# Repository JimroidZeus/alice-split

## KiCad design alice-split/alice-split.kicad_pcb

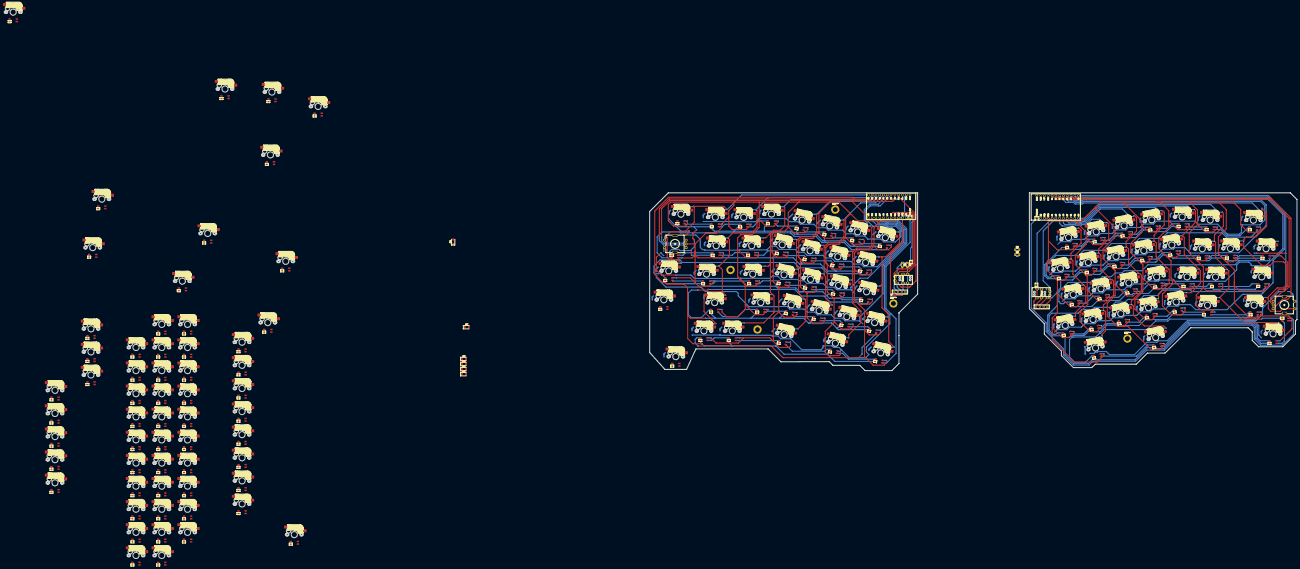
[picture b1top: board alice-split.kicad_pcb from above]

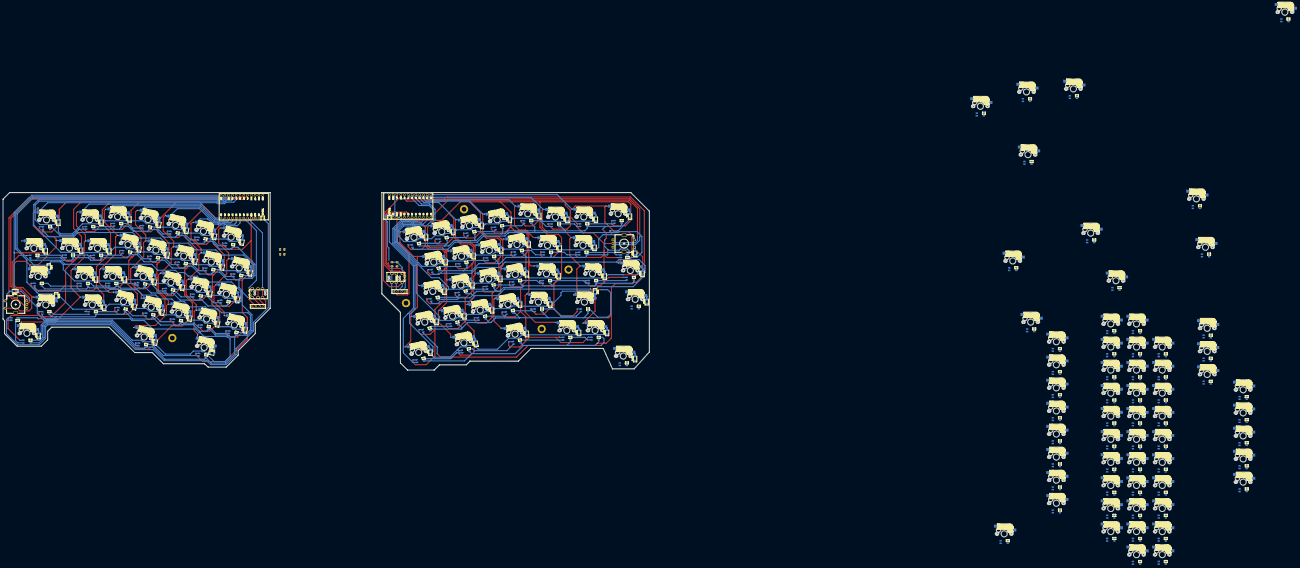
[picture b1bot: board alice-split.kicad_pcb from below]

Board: 2 copper layers, 434.2 x 119.2 mm, 215 parts (69 on the bottom side), 182 nets.

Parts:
D1, D2, D3, D4, D5, D6, D7, D8, D9, D10, D11, D12, D13, D14, D15, D16, D17, D18, D19, D20, D21, D22, D23, D24, D25, D26, D27, D28, D29, D30, D31, D32, D33, D34, D35, D36, D37, D38, D39, D40, D41, D42, D43, D44, D45, D46, D47, D48, D49, D50, D51, D52, D53, D54, D55, D56, D57, D58, D59, D60, D61, D62, D63, D64, D65, D66, D67, D68, D69, D70, D71, D72, D73, D74: D_Small; D_1206_3216Metric
D_ENC_L1: LED_sk2812_SM; SK6812MINI_underglow_dev
D_ENC_R1: LED_sk2812_SM; SK6812MINI_underglow_dev
J1, J4: MJ-4PP-9-Lily58-cache-Lily58_Pro-rescue; MJ-4PP-9
J2, J3: OLED-Lily58-cache; OLED_4Pin
JP1, JP2: Jumper-Device; Jumper
R1, R2, R3, R4: R_Small; R_1206_DoubleSided
SW38, SW39, SW40, SW41, SW42, SW43, SW44, SW45, SW46, SW47, SW48, SW49, SW50, SW51, SW52, SW53, SW54, SW55, SW56, SW57, SW58, SW59, SW60, SW61, SW62, SW63, SW64, SW65, SW66, SW67, SW68, SW69, SW70, SW71, SW72, SW73, SW74, SW75, SW76, SW77, SW78, SW79, SW80, SW81, SW82, SW83, SW84, SW85, SW86, SW87, SW88, SW89: SW_PUSH-MX_W_LED; SK6812MINI_and_cherry
SW_0, SW_1, SW_2, SW_3, SW_4, SW_5, SW_6, SW_7, SW_8, SW_9: SW_PUSH-MX_W_LED; SK6812MINI_and_cherry
SW_A1: SW_PUSH-MX_W_LED; SK6812MINI_and_cherry
SW_BCKSLSH1: SW_PUSH-MX_W_LED; SK6812MINI_and_cherry
SW_BCKSPC1: SW_PUSH-MX_W_LED; SK6812MINI_and_cherry
SW_B_L1: SW_PUSH-MX_W_LED; SK6812MINI_and_cherry
SW_B_R1: SW_PUSH-MX_W_LED; SK6812MINI_and_cherry
SW_C1: SW_PUSH-MX_W_LED; SK6812MINI_and_cherry
SW_CAPS1: SW_PUSH-MX_W_LED; SK6812MINI_and_cherry
SW_COLON1: SW_PUSH-MX_W_LED; SK6812MINI_and_cherry
SW_COMMA1: SW_PUSH-MX_W_LED; SK6812MINI_and_cherry
SW_CTRL_L1: SW_PUSH-MX_W_LED; SK6812MINI_and_cherry
SW_C_BRACE1: SW_PUSH-MX_W_LED; SK6812MINI_and_cherry
SW_D1: SW_PUSH-MX_W_LED; SK6812MINI_and_cherry
SW_E1: SW_PUSH-MX_W_LED; SK6812MINI_and_cherry
SW_ENC_L1: RotaryEncoder_Switch; RotaryEncoder_Alps_EC11E-Switch_Vertical_H20mm-keebio_modif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
SW_ENC_R1: RotaryEncoder_Switch; RotaryEncoder_Alps_EC11E-Switch_Vertical_H20mm-keebio_modif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
SW_ENTER1: SW_PUSH-MX_W_LED; SK6812MINI_and_cherry
SW_EQUALS1: SW_PUSH-MX_W_LED; SK6812MINI_and_cherry
SW_ESC1: SW_PUSH-MX_W_LED; SK6812MINI_and_cherry
SW_F1, SW_F2, SW_F3, SW_F4, SW_F5, SW_F6, SW_F7, SW_F8: SW_PUSH-MX_W_LED; SK6812MINI_and_cherry
SW_FN1: SW_PUSH-MX_W_LED; SK6812MINI_and_cherry
SW_G1: SW_PUSH-MX_W_LED; SK6812MINI_and_cherry
SW_H1: SW_PUSH-MX_W_LED; SK6812MINI_and_cherry
SW_I1: SW_PUSH-MX_W_LED; SK6812MINI_and_cherry
SW_J1: SW_PUSH-MX_W_LED; SK6812MINI_and_cherry
SW_K1: SW_PUSH-MX_W_LED; SK6812MINI_and_cherry
SW_L1: SW_PUSH-MX_W_LED; SK6812MINI_and_cherry
SW_M1: SW_PUSH-MX_W_LED; SK6812MINI_and_cherry
SW_MACRO1, SW_MACRO2, SW_MACRO3, SW_MACRO4: SW_PUSH-MX_W_LED; SK6812MINI_and_cherry
SW_MINUS1: SW_PUSH-MX_W_LED; SK6812MINI_and_cherry
SW_MOD_L1: SW_PUSH-MX_W_LED; SK6812MINI_and_cherry
SW_MOD_R1: SW_PUSH-MX_W_LED; SK6812MINI_and_cherry
SW_N1: SW_PUSH-MX_W_LED; SK6812MINI_and_cherry
SW_O1: SW_PUSH-MX_W_LED; SK6812MINI_and_cherry
SW_OPT1: SW_PUSH-MX_W_LED; SK6812MINI_and_cherry
SW_O_BRACE1: SW_PUSH-MX_W_LED; SK6812MINI_and_cherry
SW_P1: SW_PUSH-MX_W_LED; SK6812MINI_and_cherry
SW_PERIOD1: SW_PUSH-MX_W_LED; SK6812MINI_and_cherry
SW_Q1: SW_PUSH-MX_W_LED; SK6812MINI_and_cherry
SW_QUOTE1: SW_PUSH-MX_W_LED; SK6812MINI_and_cherry
SW_R1: SW_PUSH-MX_W_LED; SK6812MINI_and_cherry
SW_S1: SW_PUSH-MX_W_LED; SK6812MINI_and_cherry
SW_SHIFT_L1: SW_PUSH-MX_W_LED; SK6812MINI_and_cherry
SW_SHIFT_R1: SW_PUSH-MX_W_LED; SK6812MINI_and_cherry
SW_SLASH1: SW_PUSH-MX_W_LED; SK6812MINI_and_cherry
SW_SPC_L1: SW_PUSH-MX_W_LED; SK6812MINI_and_cherry
SW_SPC_R1: SW_PUSH-MX_W_LED; SK6812MINI_and_cherry
SW_T1: SW_PUSH-MX_W_LED; SK6812MINI_and_cherry
SW_TAB1: SW_PUSH-MX_W_LED; SK6812MINI_and_cherry
SW_TILDE1: SW_PUSH-MX_W_LED; SK6812MINI_and_cherry
SW_U1: SW_PUSH-MX_W_LED; SK6812MINI_and_cherry
SW_V1: SW_PUSH-MX_W_LED; SK6812MINI_and_cherry
SW_W1: SW_PUSH-MX_W_LED; SK6812MINI_and_cherry
SW_X1: SW_PUSH-MX_W_LED; SK6812MINI_and_cherry
SW_Y1: SW_PUSH-MX_W_LED; SK6812MINI_and_cherry
SW_Z1: SW_PUSH-MX_W_LED; SK6812MINI_and_cherry
U1: Sparkfun_Pro_Micro; ArduinoProMicro
U2: ProMicro_2-Lily58-cache-Lily58_Pro-rescue; ArduinoProMicro

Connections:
/COL0: SW_6.6, SW_B_L1.6, SW_FN1.6, SW_G1.6, SW_T1.6, U1.19 (A2(PF5))
/COL1: SW_5.6, SW_F8.6, SW_R1.6, SW_SPC_L1.6, SW_V1.6, U1.18 (A1(PF6))
/COL2: SW_4.6, SW_C1.6, SW_D1.6, SW_E1.6, SW_MOD_L1.6, U1.17 (A0(PF7))
/COL3: SW_3.6, SW_OPT1.6, SW_S1.6, SW_W1.6, SW_X1.6, U1.16 (D15(PB1))
/COL4: SW_2.6, SW_A1.6, SW_CTRL_L1.6, SW_Q1.6, SW_Z1.6, U1.15 (D14(PB3))
/COL5: SW_1.6, SW_CAPS1.6, SW_MACRO3.6, SW_SHIFT_L1.6, SW_TAB1.6, U1.14 (D16(PB2))
/COL6: SW_ENC_L1.S1, SW_ESC1.6, SW_MACRO1.6, SW_MACRO2.6, SW_TILDE1.6, U1.13 (D10(PB6))
/DATA: JP1.1, U1.2 (RX(PD2))
/ENCA: SW_ENC_L1.A, U1.20 (A3(PF4))
/ENCB: SW_ENC_L1.B, U1.12 (D9(PB5))
/ENC_S2: D38.2 (A), SW_ENC_L1.S2
/LEDs: SW_FN1.3 (DIN), U1.1 (TX(PD3))
/ROW0: D33.1 (K), D34.1 (K), D35.1 (K), D36.1 (K), D37.1 (K), D40.1 (K), D74.1 (K), U1.7 (D4(PD4))
/ROW1: D27.1 (K), D28.1 (K), D29.1 (K), D30.1 (K), D31.1 (K), D32.1 (K), D39.1 (K), U1.8 (D5(PC6))
/ROW2: D21.1 (K), D22.1 (K), D23.1 (K), D24.1 (K), D25.1 (K), D26.1 (K), D38.1 (K), U1.9 (D6(PD7))
/ROW3: D1.1 (K), D15.1 (K), D16.1 (K), D17.1 (K), D18.1 (K), D19.1 (K), D20.1 (K), U1.10 (D7(PE6))
/ROW4: D8.1 (K), D9.1 (K), D10.1 (K), D11.1 (K), D12.1 (K), D13.1 (K), D14.1 (K), U1.11 (D8(PB4))
/Right Hand Side/COL0: SW_BCKSPC1.6, SW_C_BRACE1.6, SW_ENC_R1.S1, SW_ENTER1.6, SW_SHIFT_R1.6, U2.18 (A1(PF6))
/Right Hand Side/COL1: SW_EQUALS1.6, SW_MACRO4.6, SW_O_BRACE1.6, SW_QUOTE1.6, SW_SLASH1.6, U2.12 (D9(PB5))
/Right Hand Side/COL2: SW_COLON1.6, SW_MINUS1.6, SW_P1.6, SW_PERIOD1.6, U2.11 (D8(PB4))
/Right Hand Side/COL3: SW_0.6, SW_COMMA1.6, SW_L1.6, SW_O1.6, U2.10 (D7(PE6))
/Right Hand Side/COL4: SW_9.6, SW_I1.6, SW_K1.6, SW_M1.6, SW_MOD_R1.6, U2.9 (D6(PD7))
/Right Hand Side/COL5: SW_8.6, SW_J1.6, SW_N1.6, SW_SPC_R1.6, SW_U1.6, U2.8 (D5(PC6))
/Right Hand Side/COL6: SW_7.6, SW_BCKSLSH1.6, SW_B_R1.6, SW_H1.6, SW_Y1.6, U2.7 (D4(PD4))
/Right Hand Side/DATA: JP2.2, U2.2 (RX(PD2))
/Right Hand Side/ENCA: SW_ENC_R1.A, U2.20 (A3(PF4))
/Right Hand Side/ENCB: SW_ENC_R1.B, U2.19 (A2(PF5))
/Right Hand Side/ENC_S2: D72.2 (A), SW_ENC_R1.S2
/Right Hand Side/LEDs: D_ENC_R1.3 (DIN), U2.1 (TX(PD3))
/Right Hand Side/ROW0: D55.1 (K), D70.1 (K), D71.1 (K), D72.1 (K), D73.1 (K), U2.13 (D10(PB6))
/Right Hand Side/ROW1: D63.1 (K), D64.1 (K), D65.1 (K), D66.1 (K), D67.1 (K), D68.1 (K), D69.1 (K), U2.14 (D16(PB2))
/Right Hand Side/ROW2: D56.1 (K), D57.1 (K), D58.1 (K), D59.1 (K), D60.1 (K), D61.1 (K), D62.1 (K), U2.15 (D14(PB3))
/Right Hand Side/ROW3: D48.1 (K), D49.1 (K), D50.1 (K), D51.1 (K), D52.1 (K), D53.1 (K), D54.1 (K), U2.16 (D15(PB1))
/Right Hand Side/ROW4: D41.1 (K), D42.1 (K), D43.1 (K), D44.1 (K), D45.1 (K), D46.1 (K), D47.1 (K), U2.17 (A0(PF7))
/Right Hand Side/SCL: J3.2, J4.4, R4.2, U2.6 (SCL(PD0))
/Right Hand Side/SDA: J3.1, J4.3, JP2.1, R3.2, U2.5 (SDA(PD1))
/Right Hand Side/VCC: D_ENC_R1.2 (VSS), J3.3, J4.1, R3.1, R4.1, SW_0.2 (VSS), SW_7.2 (VSS), SW_8.2 (VSS), SW_9.2 (VSS), SW_BCKSLSH1.2 (VSS), SW_BCKSPC1.2 (VSS), SW_B_R1.2 (VSS), SW_COLON1.2 (VSS), SW_COMMA1.2 (VSS), SW_C_BRACE1.2 (VSS), SW_ENTER1.2 (VSS), SW_EQUALS1.2 (VSS), SW_H1.2 (VSS), SW_I1.2 (VSS), SW_J1.2 (VSS), SW_K1.2 (VSS), SW_L1.2 (VSS), SW_M1.2 (VSS), SW_MACRO4.2 (VSS), SW_MINUS1.2 (VSS), SW_MOD_R1.2 (VSS), SW_N1.2 (VSS), SW_O1.2 (VSS), SW_O_BRACE1.2 (VSS), SW_P1.2 (VSS), SW_PERIOD1.2 (VSS), SW_QUOTE1.2 (VSS), SW_SHIFT_R1.2 (VSS), SW_SLASH1.2 (VSS), SW_SPC_R1.2 (VSS), SW_U1.2 (VSS), SW_Y1.2 (VSS), U2.21 (VCC)
/SCL: J1.4, J2.2, R2.2, U1.6 (SCL(PD0))
/SDA: J1.3, J2.1, JP1.2, R1.2, U1.5 (SDA(PD1))
/VCC: D_ENC_L1.2 (VSS), J1.1, J2.3, R1.1, R2.1, SW_1.2 (VSS), SW_2.2 (VSS), SW_3.2 (VSS), SW_4.2 (VSS), SW_5.2 (VSS), SW_6.2 (VSS), SW_A1.2 (VSS), SW_B_L1.2 (VSS), SW_C1.2 (VSS), SW_CAPS1.2 (VSS), SW_CTRL_L1.2 (VSS), SW_D1.2 (VSS), SW_E1.2 (VSS), SW_ESC1.2 (VSS), SW_F8.2 (VSS), SW_FN1.2 (VSS), SW_G1.2 (VSS), SW_MACRO1.2 (VSS), SW_MOD_L1.2 (VSS), SW_OPT1.2 (VSS), SW_Q1.2 (VSS), SW_R1.2 (VSS), SW_S1.2 (VSS), SW_SHIFT_L1.2 (VSS), SW_SPC_L1.2 (VSS), SW_T1.2 (VSS), SW_TAB1.2 (VSS), SW_TILDE1.2 (VSS), SW_V1.2 (VSS), SW_W1.2 (VSS), SW_X1.2 (VSS), SW_Z1.2 (VSS), U1.21 (VCC)
GND: D_ENC_L1.4 (VDD), D_ENC_R1.4 (VDD), J1.2, J2.4, J3.4, J4.2, SW_0.4 (VDD), SW_1.4 (VDD), SW_2.4 (VDD), SW_3.4 (VDD), SW_4.4 (VDD), SW_5.4 (VDD), SW_6.4 (VDD), SW_7.4 (VDD), SW_8.4 (VDD), SW_9.4 (VDD), SW_A1.4 (VDD), SW_BCKSLSH1.4 (VDD), SW_BCKSPC1.4 (VDD), SW_B_L1.4 (VDD), SW_B_R1.4 (VDD), SW_C1.4 (VDD), SW_CAPS1.4 (VDD), SW_COLON1.4 (VDD), SW_COMMA1.4 (VDD), SW_CTRL_L1.4 (VDD), SW_C_BRACE1.4 (VDD), SW_D1.4 (VDD), SW_E1.4 (VDD), SW_ENC_L1.C, SW_ENC_R1.C, SW_ENTER1.4 (VDD), SW_EQUALS1.4 (VDD), SW_ESC1.4 (VDD), SW_F8.4 (VDD), SW_FN1.4 (VDD), SW_G1.4 (VDD), SW_H1.4 (VDD), SW_I1.4 (VDD), SW_J1.4 (VDD), SW_K1.4 (VDD), SW_L1.4 (VDD), SW_M1.4 (VDD), SW_MACRO1.4 (VDD), SW_MACRO4.4 (VDD), SW_MINUS1.4 (VDD), SW_MOD_L1.4 (VDD), SW_MOD_R1.4 (VDD), SW_N1.4 (VDD), SW_O1.4 (VDD), SW_OPT1.4 (VDD), SW_O_BRACE1.4 (VDD), SW_P1.4 (VDD), SW_PERIOD1.4 (VDD), SW_Q1.4 (VDD), SW_QUOTE1.4 (VDD), SW_R1.4 (VDD), SW_S1.4 (VDD), SW_SHIFT_L1.4 (VDD), SW_SHIFT_R1.4 (VDD), SW_SLASH1.4 (VDD), SW_SPC_L1.4 (VDD), SW_SPC_R1.4 (VDD), SW_T1.4 (VDD), SW_TAB1.4 (VDD), SW_TILDE1.4 (VDD), SW_U1.4 (VDD), SW_V1.4 (VDD), SW_W1.4 (VDD), SW_X1.4 (VDD), SW_Y1.4 (VDD), SW_Z1.4 (VDD), U1.3 (GND), U1.4 (GND), U1.23 (GND), U2.3 (GND), U2.4 (GND), U2.23 (GND)
unnamed: D1.2 (A), SW_ESC1.5
unnamed: D2.2 (A), SW_F1.5
unnamed: D3.2 (A), SW_F2.5
unnamed: D4.2 (A), SW_F3.5
unnamed: D5.2 (A), SW_F4.5
unnamed: D6.2 (A), SW_F5.5
unnamed: D7.2 (A), SW_F6.5
unnamed: D8.2 (A), SW_6.5
unnamed: D9.2 (A), SW_5.5
unnamed: D10.2 (A), SW_4.5
unnamed: D11.2 (A), SW_3.5
unnamed: D12.2 (A), SW_2.5
unnamed: D13.2 (A), SW_1.5
unnamed: D14.2 (A), SW_TILDE1.5
unnamed: D15.2 (A), SW_TAB1.5
unnamed: D16.2 (A), SW_Q1.5
unnamed: D17.2 (A), SW_W1.5
unnamed: D18.2 (A), SW_E1.5
unnamed: D19.2 (A), SW_R1.5
unnamed: D20.2 (A), SW_T1.5
unnamed: D21.2 (A), SW_CAPS1.5
unnamed: D22.2 (A), SW_A1.5
unnamed: D23.2 (A), SW_S1.5
unnamed: D24.2 (A), SW_D1.5
unnamed: D25.2 (A), SW_F8.5
unnamed: D26.2 (A), SW_G1.5
unnamed: D27.2 (A), SW_SHIFT_L1.5
unnamed: D28.2 (A), SW_Z1.5
unnamed: D29.2 (A), SW_X1.5
unnamed: D30.2 (A), SW_C1.5
unnamed: D31.2 (A), SW_V1.5
unnamed: D32.2 (A), SW_B_L1.5
unnamed: D33.2 (A), SW_CTRL_L1.5
unnamed: D34.2 (A), SW_OPT1.5
unnamed: D35.2 (A), SW_MOD_L1.5
unnamed: D36.2 (A), SW_SPC_L1.5
unnamed: D37.2 (A), SW_FN1.5
unnamed: D39.2 (A), SW_MACRO1.5
unnamed: D40.2 (A), SW_MACRO2.5
unnamed: D41.2 (A), SW_7.5
unnamed: D42.2 (A), SW_8.5
unnamed: D43.2 (A), SW_9.5
unnamed: D44.2 (A), SW_0.5
unnamed: D45.2 (A), SW_MINUS1.5
unnamed: D46.2 (A), SW_EQUALS1.5
unnamed: D47.2 (A), SW_BCKSPC1.5
unnamed: D48.2 (A), SW_Y1.5
unnamed: D49.2 (A), SW_U1.5
unnamed: D50.2 (A), SW_I1.5
unnamed: D51.2 (A), SW_O1.5
unnamed: D52.2 (A), SW_P1.5
unnamed: D53.2 (A), SW_O_BRACE1.5
unnamed: D54.2 (A), SW_C_BRACE1.5
unnamed: D55.2 (A), SW_BCKSLSH1.5
unnamed: D56.2 (A), SW_H1.5
unnamed: D57.2 (A), SW_J1.5
unnamed: D58.2 (A), SW_K1.5
unnamed: D59.2 (A), SW_L1.5
unnamed: D60.2 (A), SW_COLON1.5
unnamed: D61.2 (A), SW_QUOTE1.5
unnamed: D62.2 (A), SW_ENTER1.5
unnamed: D63.2 (A), SW_B_R1.5
unnamed: D64.2 (A), SW_N1.5
unnamed: D65.2 (A), SW_M1.5
unnamed: D66.2 (A), SW_COMMA1.5
unnamed: D67.2 (A), SW_PERIOD1.5
unnamed: D68.2 (A), SW_SLASH1.5
unnamed: D69.2 (A), SW_SHIFT_R1.5
unnamed: D70.2 (A), SW_SPC_R1.5
unnamed: D71.2 (A), SW_MOD_R1.5
unnamed: D73.2 (A), SW_MACRO4.5
unnamed: D74.2 (A), SW_MACRO3.5
unnamed: D_ENC_L1.3 (DIN), SW_TAB1.1 (DOUT)
unnamed: D_ENC_L1.1 (DOUT), SW_6.3 (DIN)
unnamed: D_ENC_R1.1 (DOUT), SW_MACRO4.3 (DIN)
unnamed: SW_0.3 (DIN), SW_MINUS1.1 (DOUT)
unnamed: SW_0.1 (DOUT), SW_9.3 (DIN)
unnamed: SW_1.3 (DIN), SW_2.1 (DOUT)
unnamed: SW_1.1 (DOUT), SW_TILDE1.3 (DIN)
unnamed: SW_2.3 (DIN), SW_3.1 (DOUT)
unnamed: SW_3.3 (DIN), SW_4.1 (DOUT)
unnamed: SW_4.3 (DIN), SW_5.1 (DOUT)
unnamed: SW_5.3 (DIN), SW_6.1 (DOUT)
unnamed: SW_7.3 (DIN), SW_8.1 (DOUT)
unnamed: SW_8.3 (DIN), SW_9.1 (DOUT)
unnamed: SW_A1.3 (DIN), SW_S1.1 (DOUT)
unnamed: SW_A1.1 (DOUT), SW_CAPS1.3 (DIN)
unnamed: SW_BCKSLSH1.3 (DIN), SW_H1.1 (DOUT)
unnamed: SW_BCKSLSH1.1 (DOUT), SW_C_BRACE1.3 (DIN)
unnamed: SW_BCKSPC1.3 (DIN), SW_Y1.1 (DOUT)
unnamed: SW_BCKSPC1.1 (DOUT), SW_EQUALS1.3 (DIN)
unnamed: SW_B_L1.3 (DIN), SW_CTRL_L1.1 (DOUT)
unnamed: SW_B_L1.1 (DOUT), SW_V1.3 (DIN)
unnamed: SW_B_R1.3 (DIN), SW_N1.1 (DOUT)
unnamed: SW_B_R1.1 (DOUT), SW_ENTER1.3 (DIN)
unnamed: SW_C1.3 (DIN), SW_V1.1 (DOUT)
unnamed: SW_C1.1 (DOUT), SW_X1.3 (DIN)
unnamed: SW_CAPS1.1 (DOUT), SW_MACRO1.3 (DIN)
unnamed: SW_COLON1.3 (DIN), SW_QUOTE1.1 (DOUT)
unnamed: SW_COLON1.1 (DOUT), SW_L1.3 (DIN)
unnamed: SW_COMMA1.3 (DIN), SW_PERIOD1.1 (DOUT)
unnamed: SW_COMMA1.1 (DOUT), SW_M1.3 (DIN)
unnamed: SW_CTRL_L1.3 (DIN), SW_OPT1.1 (DOUT)
unnamed: SW_C_BRACE1.1 (DOUT), SW_O_BRACE1.3 (DIN)
unnamed: SW_D1.3 (DIN), SW_F8.1 (DOUT)
unnamed: SW_D1.1 (DOUT), SW_S1.3 (DIN)
unnamed: SW_E1.3 (DIN), SW_R1.1 (DOUT)
unnamed: SW_E1.1 (DOUT), SW_W1.3 (DIN)
unnamed: SW_ENTER1.1 (DOUT), SW_QUOTE1.3 (DIN)
unnamed: SW_EQUALS1.1 (DOUT), SW_MINUS1.3 (DIN)
unnamed: SW_ESC1.3 (DIN), SW_TILDE1.1 (DOUT)
unnamed: SW_F1.3 (DIN), SW_F2.1 (DOUT)
unnamed: SW_F2.3 (DIN), SW_F3.1 (DOUT)
unnamed: SW_F3.3 (DIN), SW_F4.1 (DOUT)
unnamed: SW_F4.3 (DIN), SW_F5.1 (DOUT)
unnamed: SW_F5.3 (DIN), SW_F6.1 (DOUT)
unnamed: SW_F8.3 (DIN), SW_G1.1 (DOUT)
unnamed: SW_FN1.1 (DOUT), SW_SPC_L1.3 (DIN)
unnamed: SW_G1.3 (DIN), SW_SHIFT_L1.1 (DOUT)
unnamed: SW_H1.3 (DIN), SW_J1.1 (DOUT)
unnamed: SW_I1.3 (DIN), SW_O1.1 (DOUT)
unnamed: SW_I1.1 (DOUT), SW_U1.3 (DIN)
unnamed: SW_J1.3 (DIN), SW_K1.1 (DOUT)
unnamed: SW_K1.3 (DIN), SW_L1.1 (DOUT)
unnamed: SW_M1.1 (DOUT), SW_N1.3 (DIN)
unnamed: SW_MACRO1.1 (DOUT), SW_T1.3 (DIN)
unnamed: SW_MACRO4.1 (DOUT), SW_MOD_R1.3 (DIN)
unnamed: SW_MOD_L1.3 (DIN), SW_SPC_L1.1 (DOUT)
unnamed: SW_MOD_L1.1 (DOUT), SW_OPT1.3 (DIN)
unnamed: SW_MOD_R1.1 (DOUT), SW_SPC_R1.3 (DIN)
unnamed: SW_O1.3 (DIN), SW_P1.1 (DOUT)
unnamed: SW_O_BRACE1.1 (DOUT), SW_P1.3 (DIN)
unnamed: SW_PERIOD1.3 (DIN), SW_SLASH1.1 (DOUT)
unnamed: SW_Q1.3 (DIN), SW_W1.1 (DOUT)
unnamed: SW_Q1.1 (DOUT), SW_TAB1.3 (DIN)
unnamed: SW_R1.3 (DIN), SW_T1.1 (DOUT)
unnamed: SW_SHIFT_L1.3 (DIN), SW_Z1.1 (DOUT)
unnamed: SW_SHIFT_R1.3 (DIN), SW_SPC_R1.1 (DOUT)
unnamed: SW_SHIFT_R1.1 (DOUT), SW_SLASH1.3 (DIN)
unnamed: SW_U1.1 (DOUT), SW_Y1.3 (DIN)
unnamed: SW_X1.1 (DOUT), SW_Z1.3 (DIN)

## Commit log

2025-07-03 Initial commit. Most of the way through the left hand side schematic.
2025-07-05 Drew curved traces instead of the usual defaults. Not sure I like it. Going to branch and try again.
2025-07-05 Redid the traces but with the usual 45 degree traces. Looks nicer, made more progress.
2025-07-06 Added encoder and macro keys. Whole lefthand side is wired. Needs another review.
2025-07-06 Finished wiring encoder and macros. Fine tuning.
2025-07-06 Moved things around a little bit
2025-07-06 Changed size of keep out areas to remove some errors about pads being too close.
2025-07-07 Updating .gitignore
2025-07-07 Updating repo after adding the backups to the gitignore file.
2025-07-07 Fiddling with the ignore file path to see if it will work properly.
2025-07-07 One last time.
2025-07-07 One last time again!
2025-07-07 It was the leading ./ that was making it not work.
2025-07-07 Wired the TRRS connector. Updated a few other things too.
2025-07-08 Added jumper for OLED and wired it.
2025-07-09 Started working on the right half of the keyboard.
2025-07-09 Cleaning up some unnecessary swap files.
2025-07-10 Added vias. Finished bottom side for now. Started working on the topside.
2025-07-10 Working on cleaning up all traces on RHS. Will work on LHS after that.
2025-07-13 Rewired Left Hand Side and Edge Cuts
    Rewired the entire left hand side of the keyboard. Also added the edge cuts for the outer shape of each board. Redid this part on the left hand side to make it match the design of the right hand side.
    Will start working on the rewiring of the right hand side next.
2025-07-13 SolidWorks Part Files
    Adding SolidWorks part files including:
    - Middle plate for left hand side.
    - Middle plate for right hand side.
2025-07-17 Working on making the outer profiles of the PCBs more consistent with each other design wise.
2025-07-17 Started trying to re-arrange the left hand side macro keys.
2025-07-19 Working on adding more macro keys to the left hand side.
2025-07-20 Working on lining up the left hand side macros in a similar way to how the right hand side macros are laid out.
2025-07-22 Macro 2 and Macro 3 Placement
    - Rearranged placement of macro 2 and macro 3 in the schematic.
    - Started updating the wiring.
2025-07-23 Minor updates to the macro key traces on lhs.
